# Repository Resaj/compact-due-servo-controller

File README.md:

# Compact Due servo controller
This is a redesigned Arduino Due for the control of any humanoid or articulated robot, controlled by PS3 bluetooth controller, with bluetooth dongle in the native port of the SAM3 microcontroller, 20 servomotor signals, UART and I2C for bus servomotors.

## Authors
[Rubén Espino San José](https://github.com/Resaj)

[Mario Luis Álvarez Pastor](https://github.com/AxomirUxsil)

## License

Todos estos productos están liberados mediante [Creative Commons Attribution-ShareAlike 4.0 International License](http://creativecommons.org/licenses/by-sa/4.0/).  
_All these products are released under [Creative Commons Attribution-ShareAlike 4.0 International License](http://creativecommons.org/licenses/by-sa/4.0/)._

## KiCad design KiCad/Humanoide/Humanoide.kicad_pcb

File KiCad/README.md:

To view all 3D components of the PCB, copy the Humanoide.3dshapes folder to the folder indicates by KISYS3DMOD path.
You can find KISYS3DMOD path in Preferences->Path configuration

On Windows the path should be: C:\Program Files\KiCad\share\kicad\modules\packages3d

On GNU/Linux the path should be: /usr/share/kicad/modules/packages3d

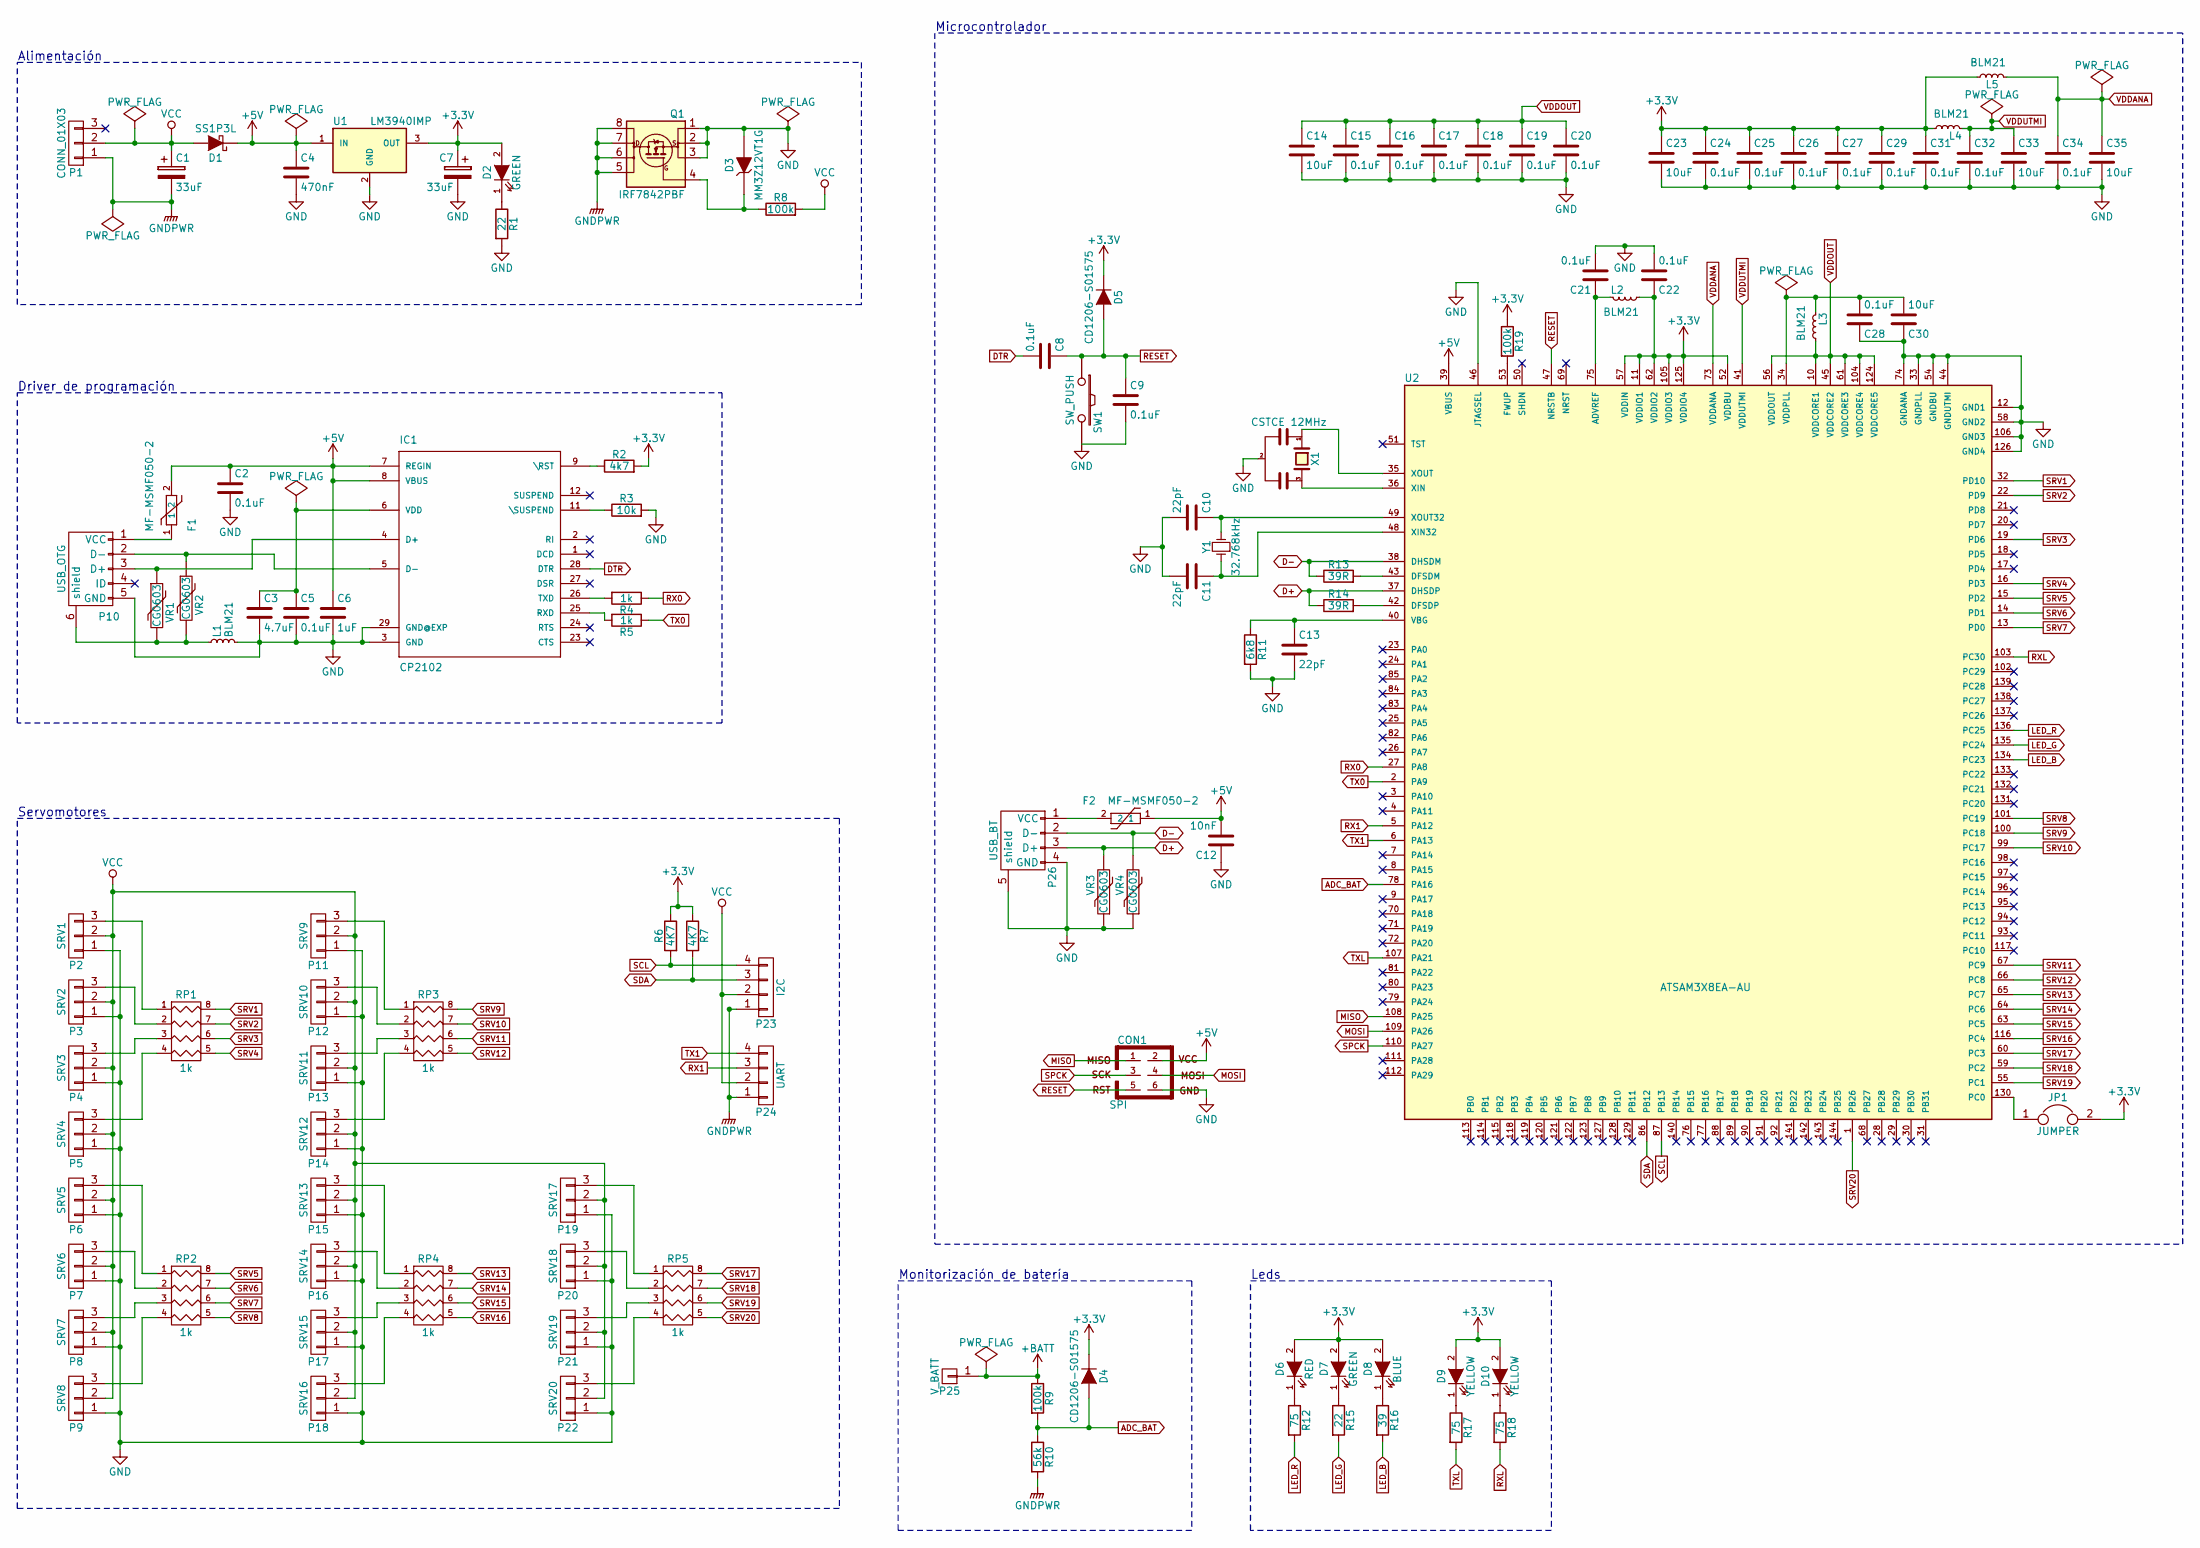
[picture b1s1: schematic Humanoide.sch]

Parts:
C1, C7: 33uF; c_elec_4x4.5
C2, C5, C8, C9, C15, C16, C17, C18, C19, C20, C21, C22, C24, C25, C26, C27, C28, C29, C31, C32, C34: 0.1uF; C_0603
C3: 4.7uF; C_0603
C4: 470nF; C_0603
C6: 1uF; C_0603
C10, C11, C13: 22pF; C_0603
C12: 10nF; C_0603
C14, C23, C30, C33, C35: 10uF; C_0603
CON1: SPI; Pin_Header_Straight_2x03_Pitch2.00mm
D1: SS1P3L; DO-220AA
D2, D7: GREEN; LED_0603
D3: MM3Z12VT1G; SOD-323
D4, D5: CD1206-S01575; SMD-1206_Pol
D6: RED; LED_0603
D8: BLUE; LED_0603
D9, D10: YELLOW; LED_0603
F1, F2: MF-MSMF050-2; Fuse_SMD
IC1: CP2102; QFN-28-1EP_5x5mm_Pitch0.5mm
JP1: JUMPER; Fuse_SMD1206_Wave
L1, L2, L3, L4, L5: BLM21; R_0805_HandSoldering
P1: CONN_01X03; Pin_Header_Angled_1x03
P2: SRV1; Pin_Header_Straight_1x03
P3: SRV2; Pin_Header_Straight_1x03
P4: SRV3; Pin_Header_Straight_1x03
P5: SRV4; Pin_Header_Straight_1x03
P6: SRV5; Pin_Header_Straight_1x03
P7: SRV6; Pin_Header_Straight_1x03
P8: SRV7; Pin_Header_Straight_1x03
P9: SRV8; Pin_Header_Straight_1x03
P10: USB_OTG; USB_micro-B
P11: SRV9; Pin_Header_Straight_1x03
P12: SRV10; Pin_Header_Straight_1x03
P13: SRV11; Pin_Header_Straight_1x03
P14: SRV12; Pin_Header_Straight_1x03
P15: SRV13; Pin_Header_Straight_1x03
P16: SRV14; Pin_Header_Straight_1x03
P17: SRV15; Pin_Header_Straight_1x03
P18: SRV16; Pin_Header_Straight_1x03
P19: SRV17; Pin_Header_Straight_1x03
P20: SRV18; Pin_Header_Straight_1x03
P21: SRV19; Pin_Header_Straight_1x03
P22: SRV20; Pin_Header_Straight_1x03
P23: I2C; Molex_KK-6410-04_04x2.54mm_Straight
P24: UART; Molex_KK-6410-04_04x2.54mm_Straight
P25: V_BATT; Pin_Header_Straight_1x01
P26: USB_BT; USB-A-SMD
Q1: IRF7842PBF; SOIC-8-N
R1, R15: 22; R_0603
R2: 4k7; R_0603
R3: 10k; R_0603
R4, R5: 1k; R_0603
R6, R7: 4K7; R_0603
R8, R9, R19: 100k; R_0603
R10: 56k; R_0603
R11: 6k8; R_0603
R12, R17, R18: 75; R_0603
R13, R14: 39R; R_0603
R16: 39; R_0603
RP1, RP2, RP3, RP4, RP5: 1k; R_Array_Convex_4x0603
SW1: SW_PUSH; SW_SPST_FSMSM
U1: LM3940IMP; SOT-223
U2: ATSAM3X8EA-AU; LQFP-144_20x20mm_Pitch0.5mm
VR1, VR2, VR3, VR4: CG0603; R_0603
X1: CSTCE 12MHz; Resonator_3.2x1.3mm
Y1: 32.768kHz; Crystal_Round_Horizontal_3mm

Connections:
+3V3: C7.1, C22.1, C23.1, C24.1, C25.1, C26.1, C27.1, C29.1, C31.1, D2.2 (A), D4.1 (K), D5.1 (K), D6.2 (A), D7.2 (A), D8.2 (A), D9.2 (A), D10.2 (A), JP1.2, L2.1, L4.1, L5.1, R2.2, R6.1, R7.1, R19.1, U1.3 (OUT), U2.11 (VDDIO1), U2.52 (VDDBU), U2.57 (VDDIN), U2.62 (VDDIO2), U2.105 (VDDIO3), U2.125 (VDDIO4)
+5V: C2.1, C4.1, C6.1, C12.2, CON1.2, D1.1 (K), F1.2, F2.1, IC1.7 (REGIN), IC1.8 (VBUS), U1.1 (IN), U2.39 (VBUS)
+BATT: P25.1, R9.1
ADC_BAT: D4.2 (A), R9.2, R10.1, U2.78 (PA16)
D+: P26.3 (D+), R14.1, U2.37 (DHSDP), VR3.2
D-: P26.2 (D-), R13.1, U2.38 (DHSDM), VR4.2
DTR: C8.2, IC1.28 (DTR)
GND: C2.2, C3.2, C4.2, C5.2, C6.2, C7.2, C9.2, C10.2, C11.2, C12.1, C13.2, C14.2, C15.2, C16.2, C17.2, C18.2, C19.2, C20.2, C21.2, C22.2, C23.2, C24.2, C25.2, C26.2, C27.2, C28.1, C29.2, C30.1, C31.2, C32.2, C33.2, C34.2, C35.2, CON1.6, D3.2 (A), IC1.3 (GND), IC1.29 (GND@EXP), L1.2, P2.1, P3.1, P4.1, P5.1, P6.1, P7.1, P8.1, P9.1, P10.5 (GND), P11.1, P12.1, P13.1, P14.1, P15.1, P16.1, P17.1, P18.1, P19.1, P20.1, P21.1, P22.1, P26.4 (GND), P26.5 (shield), Q1.1 (S), Q1.2 (S), Q1.3 (S), R1.2, R3.2, R11.2, SW1.2, U1.2 (GND), U2.12 (GND1), U2.33 (GNDPLL), U2.44 (GNDUTMI), U2.46 (JTAGSEL), U2.54 (GNDBU), U2.58 (GND2), U2.74 (GNDANA), U2.106 (GND3), U2.126 (GND4), VR3.1, VR4.1, X1.2
GNDPWR: C1.2, P1.1, P23.1, P24.1, Q1.5 (D), Q1.6 (D), Q1.7 (D), Q1.8 (D), R10.2
LED_B: R16.2, U2.134 (PC23)
LED_G: R15.2, U2.135 (PC24)
LED_R: R12.2, U2.136 (PC25)
MISO: CON1.1, U2.108 (PA25)
MOSI: CON1.4, U2.109 (PA26)
unnamed: C3.1, C5.1, IC1.6 (VDD)
unnamed: C10.1, U2.49 (XOUT32), Y1.2
unnamed: C11.1, U2.48 (XIN32), Y1.1
unnamed: C13.1, R11.1, U2.40 (VBG)
unnamed: C21.1, L2.2, U2.75 (ADVREF)
unnamed: C28.2, C30.2, L3.2, U2.34 (VDDPLL)
unnamed: D2.1 (K), R1.1
unnamed: D3.1 (K), Q1.4 (G), R8.1
unnamed: D6.1 (K), R12.1
unnamed: D7.1 (K), R15.1
unnamed: D8.1 (K), R16.1
unnamed: D9.1 (K), R17.1
unnamed: D10.1 (K), R18.1
unnamed: F1.1, P10.1 (VCC)
unnamed: F2.2, P26.1 (VCC)
unnamed: IC1.4 (D+), P10.3 (D+), VR1.1
unnamed: IC1.5 (D-), P10.2 (D-), VR2.1
unnamed: IC1.9 (\RST), R2.1
unnamed: IC1.11 (\SUSPEND), R3.1
unnamed: IC1.25 (RXD), R5.2
unnamed: IC1.26 (TXD), R4.2
unnamed: JP1.1, U2.130 (PC0)
unnamed: L1.1, P10.6 (shield), VR1.2, VR2.2
unnamed: P2.3, RP1.1
unnamed: P3.3, RP1.2
unnamed: P4.3, RP1.3
unnamed: P5.3, RP1.4
unnamed: P6.3, RP2.1
unnamed: P7.3, RP2.2
unnamed: P8.3, RP2.3
unnamed: P9.3, RP2.4
unnamed: P11.3, RP3.1
unnamed: P12.3, RP3.2
unnamed: P13.3, RP3.3
unnamed: P14.3, RP3.4
unnamed: P15.3, RP4.1
unnamed: P16.3, RP4.2
unnamed: P17.3, RP4.3
unnamed: P18.3, RP4.4
unnamed: P19.3, RP5.1
unnamed: P20.3, RP5.2
unnamed: P21.3, RP5.3
unnamed: P22.3, RP5.4
unnamed: R13.2, U2.43 (DFSDM)
unnamed: R14.2, U2.42 (DFSDP)
unnamed: R19.2, U2.53 (FWUP)
unnamed: U2.35 (XOUT), X1.1
unnamed: U2.36 (XIN), X1.3
RESET: C8.1, C9.1, CON1.5, D5.2 (A), SW1.1, U2.47 (NRSTB)
RX0: R4.1, U2.27 (PA8)
RX1: P24.3, U2.5 (PA12)
RXL: R18.2, U2.103 (PC30)
SCL: P23.4, R6.2, U2.87 (PB13)
SDA: P23.3, R7.2, U2.86 (PB12)
SPCK: CON1.3, U2.110 (PA27)
SRV1: RP1.8 (R1), U2.32 (PD10)
SRV2: RP1.7 (R2), U2.22 (PD9)
SRV3: RP1.6 (R3), U2.19 (PD6)
SRV4: RP1.5 (R4), U2.16 (PD3)
SRV5: RP2.8 (R1), U2.15 (PD2)
SRV6: RP2.7 (R2), U2.14 (PD1)
SRV7: RP2.6 (R3), U2.13 (PD0)
SRV8: RP2.5 (R4), U2.101 (PC19)
SRV9: RP3.8 (R1), U2.100 (PC18)
SRV10: RP3.7 (R2), U2.99 (PC17)
SRV11: RP3.6 (R3), U2.67 (PC9)
SRV12: RP3.5 (R4), U2.66 (PC8)
SRV13: RP4.8 (R1), U2.65 (PC7)
SRV14: RP4.7 (R2), U2.64 (PC6)
SRV15: RP4.6 (R3), U2.63 (PC5)
SRV16: RP4.5 (R4), U2.116 (PC4)
SRV17: RP5.8 (R1), U2.60 (PC3)
SRV18: RP5.7 (R2), U2.59 (PC2)
SRV19: RP5.6 (R3), U2.55 (PC1)
SRV20: RP5.5 (R4), U2.1 (PB26)
TX0: R5.1, U2.2 (PA9)
TX1: P24.4, U2.6 (PA13)
TXL: R17.2, U2.107 (PA21)
VCC: C1.1, D1.2 (A), P1.2, P2.2, P3.2, P4.2, P5.2, P6.2, P7.2, P8.2, P9.2, P11.2, P12.2, P13.2, P14.2, P15.2, P16.2, P17.2, P18.2, P19.2, P20.2, P21.2, P22.2, P23.2, P24.2, R8.2
VDDANA: C34.1, C35.1, L5.2, U2.73 (VDDANA)
VDDOUT: C14.1, C15.1, C16.1, C17.1, C18.1, C19.1, C20.1, L3.1, U2.10 (VDDCORE1), U2.45 (VDDCORE2), U2.56 (VDDOUT), U2.61 (VDDCORE3), U2.104 (VDDCORE4), U2.124 (VDDCORE5)
VDDUTMI: C32.1, C33.1, L4.2, U2.41 (VDDUTMI)

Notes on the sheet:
Alimentación
Driver de programación
Servomotores
Microcontrolador
Leds
Monitorización de batería

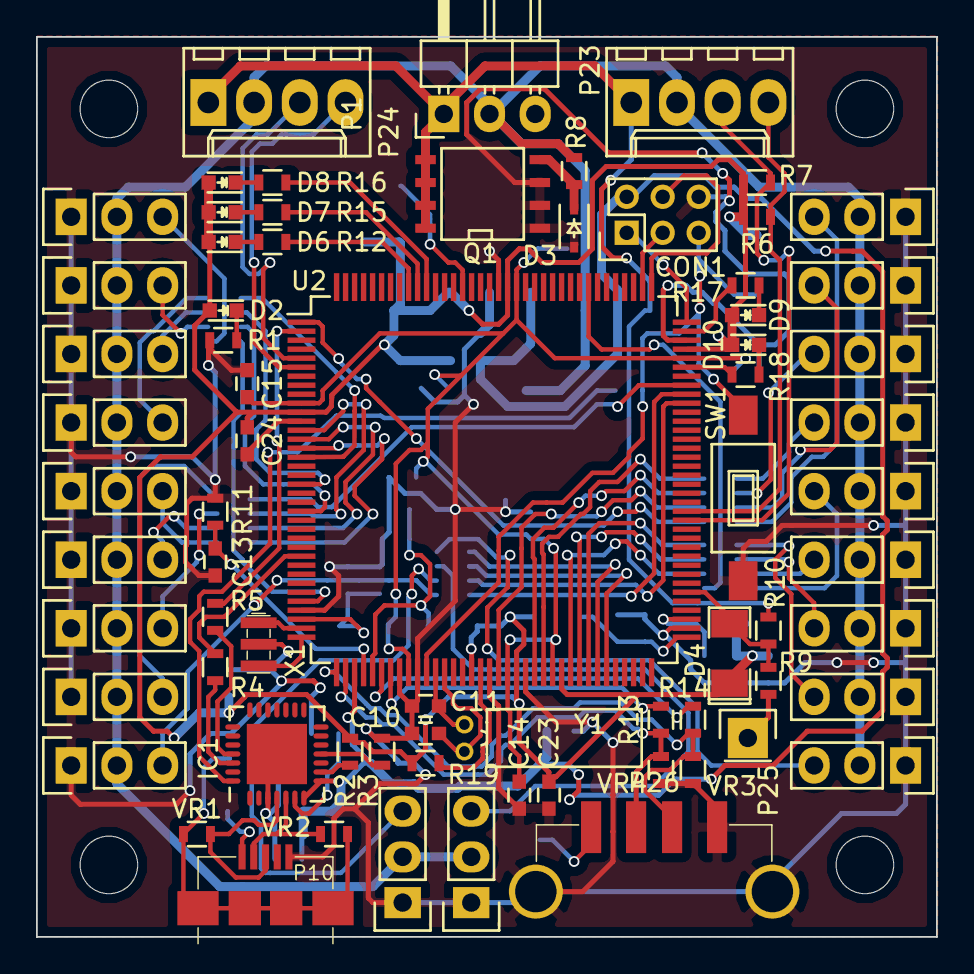
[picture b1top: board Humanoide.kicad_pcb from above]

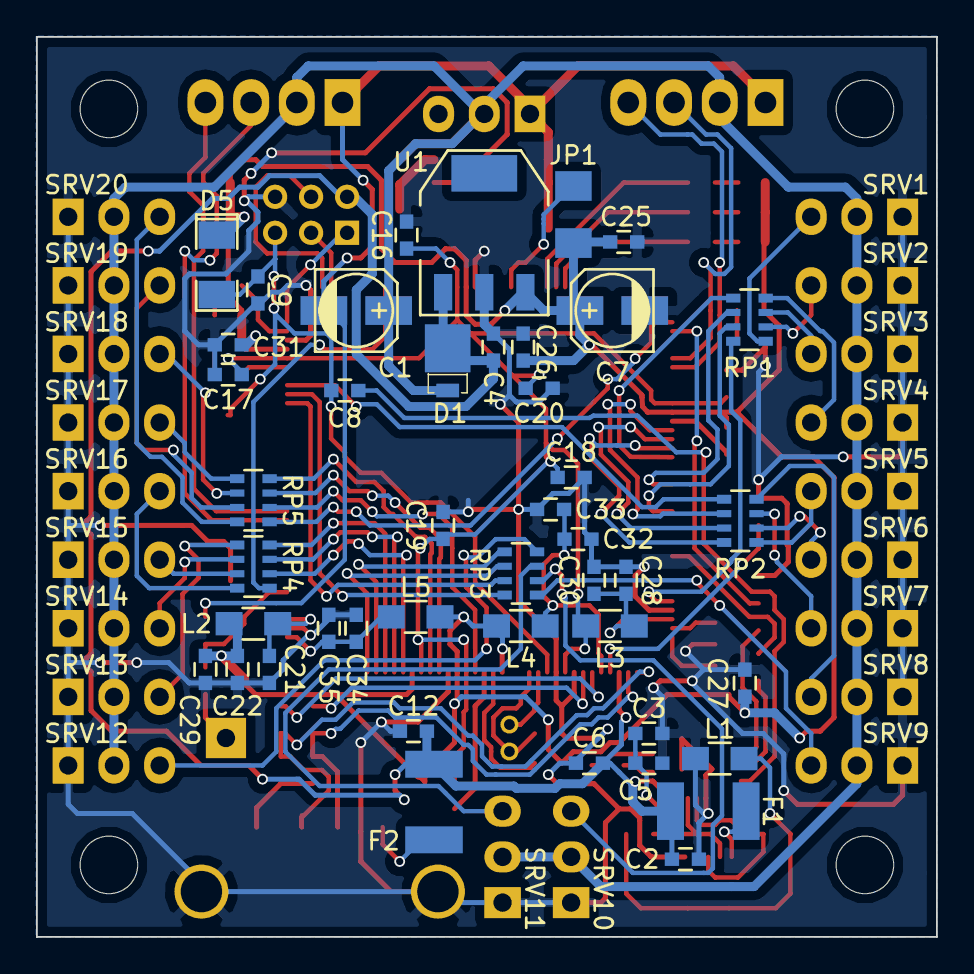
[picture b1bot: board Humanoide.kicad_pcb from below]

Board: 2 copper layers, 50.0 x 50.0 mm, 115 parts (44 on the bottom side), 96 nets.

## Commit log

2017-03-06 Update Kicad Readme
2017-03-08 PCB actualized with relative paths
2017-03-10 Kicad 3D model changed
2017-04-04 3D PCB model added
2017-12-01 Example program adapted for Arduino Due
2017-12-01 Readme modified
2018-10-17 Schematic added
2018-10-17 project reorganized
